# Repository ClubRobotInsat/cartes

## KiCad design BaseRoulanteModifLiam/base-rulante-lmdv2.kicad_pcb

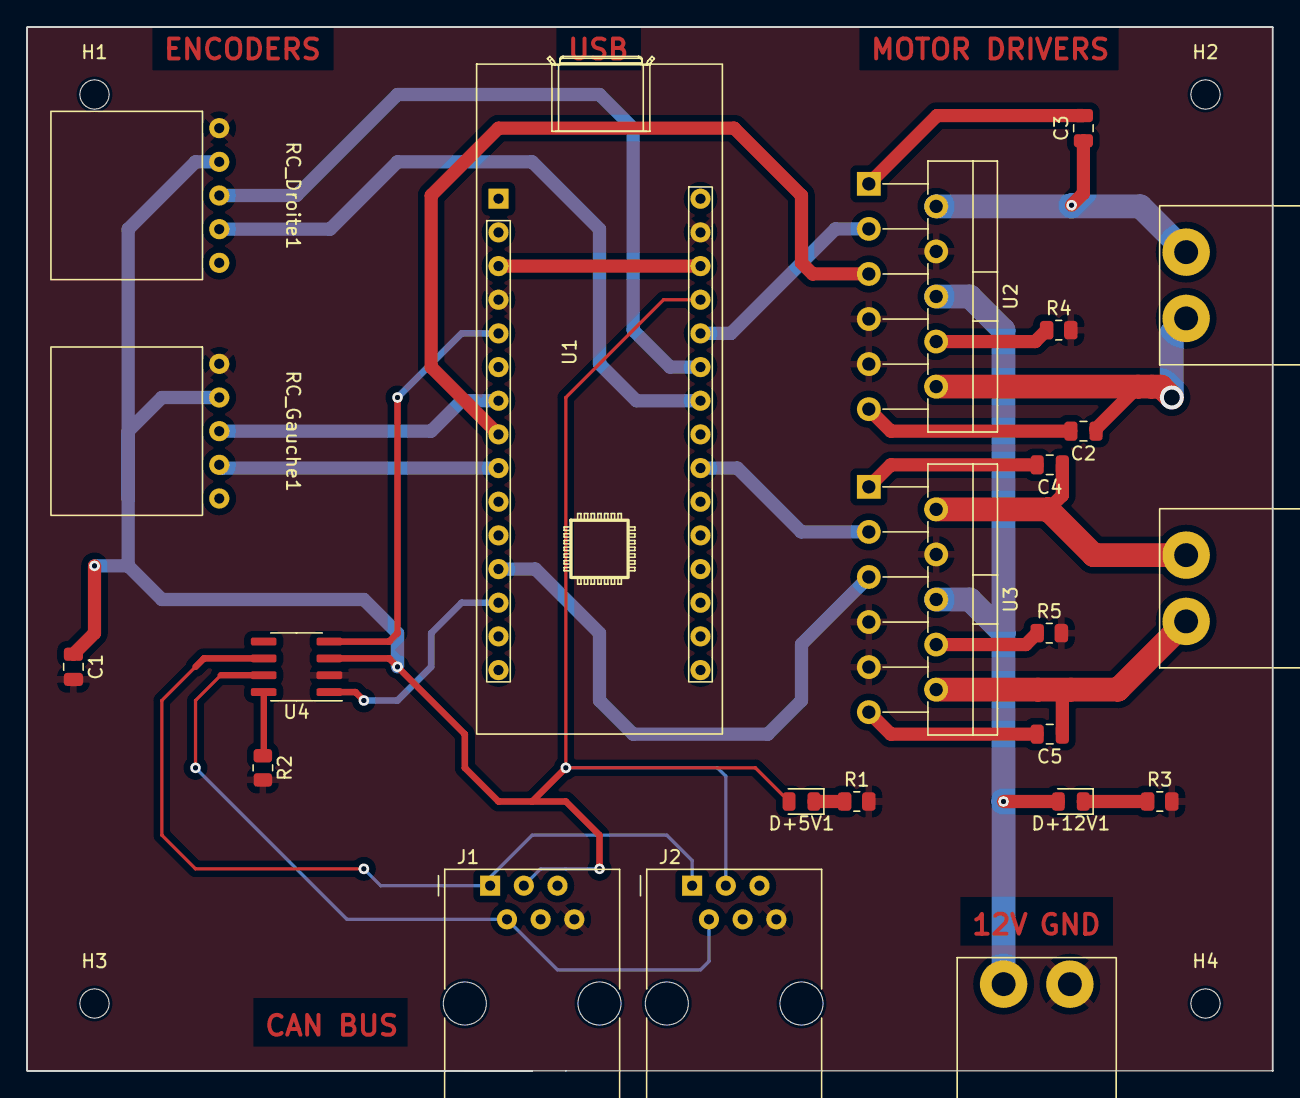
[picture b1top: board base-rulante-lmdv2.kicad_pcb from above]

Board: 2 copper layers, 94.0 x 78.7 mm, 27 parts (0 on the bottom side), 29 nets.

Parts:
C1, C2, C3, C4, C5: C_Polarized; C_0805_2012Metric
D+5V1, D+12V1: LED; LED_0805_2012Metric
H1, H2, H3, H4: MountingHole; MountingHole_2.2mm_M2
J1, J2: RJ_can; RJ12
J3, J4, J5: connector_power; WR_TBL_3137_2pins
R1, R2, R3, R4, R5: R; R_0805_2012Metric
RC_Droite1: roues_codeuses; HE14-5-angle
RC_Gauche1: roues_codeuses; HE14-5-angle
U1: Nucleo_STM32G431KB
U2, U3: LMD18200; TO-220-11_P3.4x5.08mm_StaggerOdd_Lead4.85mm_Vertical
U4: MCP2551-I-SN; SOIC-8_3.9x4.9mm_P1.27mm

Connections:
+5V: C1.1, D+5V1.2 (A), J1.3 (+5V), J2.3 (+5V), RC_Droite1.2 (+5V), RC_Gauche1.2 (+5V), U1.27 (+5V), U4.3 (VDD)
+12V: D+12V1.2 (A), J3.1 (+12V), U2.6 (VS), U3.6 (VS)
A_D: RC_Droite1.3 (A), U1.25 (PA7)
A_G: RC_Gauche1.3 (A), U1.7 (PB7)
B_D: RC_Droite1.4 (B), U1.24 (PA6/PA15)
B_G: RC_Gauche1.4 (B), U1.9 (PB6)
CANH: J1.2 (CANH), J2.2 (CANH), U4.7 (CANH)
CANL: J1.1 (CANL), J2.1 (CANL), U4.6 (CANL)
CAN_RX: U1.5 (PA12), U4.4 (RXD)
CAN_TX: U1.13 (PA11), U4.1 (TXD)
DIR_D: U1.26 (PA2), U2.3 (DIRECTION)
DIR_G: U1.22 (PA4), U3.3 (DIRECTION)
GND: C1.2, J1.6 (GND), J2.6 (GND), J3.2 (GND), R1.2, R2.2, R3.2, R4.2, R5.2, RC_Droite1.1 (GND), RC_Gauche1.1 (GND), U1.4 (GND), U1.29 (GND), U2.4 (BRAKE), U2.7 (GND), U2.9 (~THERMAL_FLAG_OUTPUT), U3.4 (BRAKE), U3.7 (GND), U3.9 (~THERMAL_FLAG_OUTPUT), U4.2 (VSS)
Mot_D_Out1: C3.1, J4.2 (GND), U2.2 (OUTPUT1)
Mot_D_Out2: C2.1, J4.1 (+12V), U2.10 (OUTPUT2)
Mot_G_Out1: C4.1, J5.2 (GND), U3.2 (OUTPUT1)
Mot_G_Out2: C5.1, J5.1 (+12V), U3.10 (OUTPUT2)
unnamed: D+5V1.1 (K), R1.1
unnamed: D+12V1.1 (K), R3.1
unnamed: U1.3 (~RST), U1.28 (~RST)
unnamed: C3.2, U2.1 (BOOTSTRAP1)
unnamed: C2.2, U2.11 (BOOTSTRAP2)
unnamed: R4.1, U2.8 (CURRENT_SENSE_OUTPUT)
unnamed: C4.2, U3.1 (BOOTSTRAP1)
unnamed: C5.2, U3.11 (BOOTSTRAP2)
unnamed: R5.1, U3.8 (CURRENT_SENSE_OUTPUT)
unnamed: R2.1, U4.8 (Rs)
PWM_D: U1.8 (PA15), U2.5 (PWM)
PWM_G: U1.12 (PA8), U3.5 (PWM)

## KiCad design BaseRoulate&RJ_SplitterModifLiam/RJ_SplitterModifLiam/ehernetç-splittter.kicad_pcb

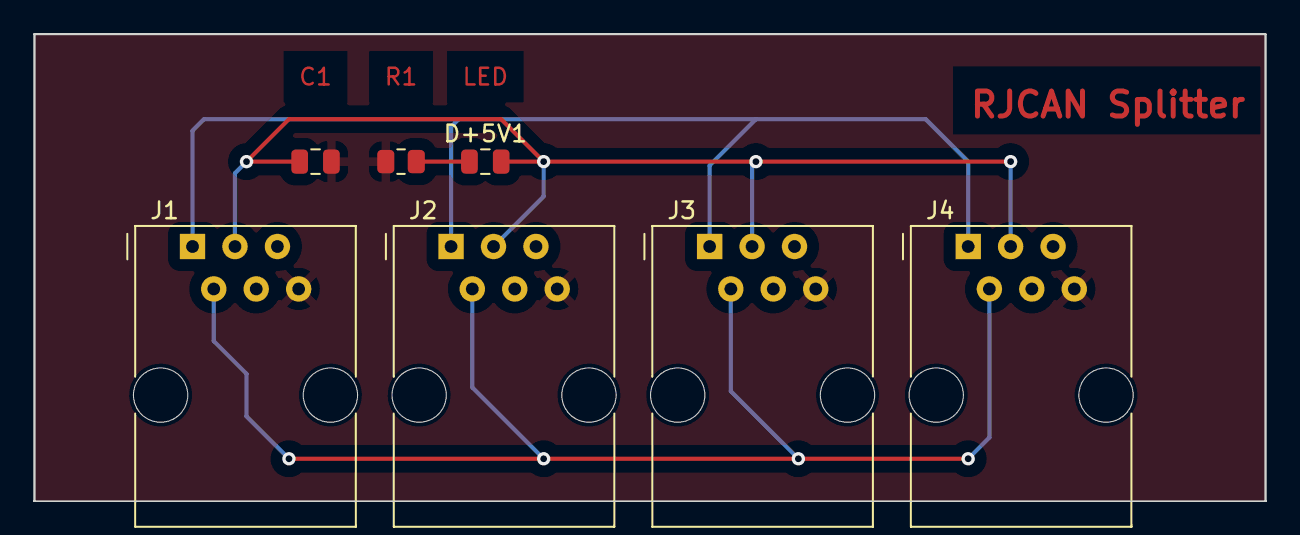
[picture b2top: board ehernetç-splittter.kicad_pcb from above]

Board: 2 copper layers, 73.7 x 27.9 mm, 7 parts (0 on the bottom side), 5 nets.

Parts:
C1: C_Polarized; C_0805_2012Metric
D+5V1: LED; C_0805_2012Metric
J1, J2, J3, J4: RJ_can; RJ12
R1: R; R_0805_2012Metric

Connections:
+5V: C1.1, D+5V1.2 (A), J1.3 (+5V), J2.3 (+5V), J3.3 (+5V), J4.3 (+5V)
CANH: J1.2 (CANH), J2.2 (CANH), J3.2 (CANH), J4.2 (CANH)
CANL: J1.1 (CANL), J2.1 (CANL), J3.1 (CANL), J4.1 (CANL)
GND: C1.2, J1.6 (GND), J2.6 (GND), J3.6 (GND), J4.6 (GND), R1.2
unnamed: D+5V1.1 (K), R1.1
